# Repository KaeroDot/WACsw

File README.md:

# WACsw - software for Wideband AC quantum tracebility

Software and documentation for measurement method using Programmable Josephson Voltage Standard to calibrate AC voltage up to 100 kHz.
Developed in the scope of EPM project *23RPT01 WAC - Wideband AC quantum traceability*

[https://www.cem.es/es/WAC](https://www.cem.es/es/WAC)

## Links

[QWTB](https://qwtb.github.io/qwtb/)

[TWM](https://github.com/smaslan/TWM)

[TWM builds](https://github.com/smaslan/TWM-builds)

## Parts

### Filter function meter

*FFmeter* measures transfer function of a digitizer using AC-AC transfer method.

[Builds are here](https://github.com/KaeroDot/WACsw/tree/master/control_software/Filter%20function%20meter%20builds)

[How to install and run](https://github.com/KaeroDot/WACsw/blob/master/control_software/Filter%20function%20meter%20builds/How%20to%20install%20and%20run%20FFmeter.md)

### Data processing scheme

Scheme is in a [separate document](https://github.com/KaeroDot/WACsw/blob/master/doc/WACsw_requirements.md)

## Status of the project

Yet to do:

Type | Task | status
-----|------|--------
WACsw | basic structure | ✔
WACsw | schematics, templates | ✔
WACsw | measurement tests | ✔
WACsw | documentation | ½ (tooltips ok, how to ok, video missing)
WACsw | add calibrator Fluke 5720A | ✔
WACsw | add calibrator Fluke 5730A | ✔
WACsw | add source AFG3110C | ½ (not yet tested)
WACsw | add AC/DC standard corrections | ½ (works in script, missing in template)
WACsw | start result calculation from GUI (using script) | ✔
WACsw | finalize fitting of frequency response - find out best method | ✔ - splines
WACsw | ❗suggestion - alternate sampling and dc measurement instead of simultaneous | must be thought out
WACsw | ❗suggestion - measurement of sensitivity at the start | must be thought out
WACsw | ❗suggestion - implement K2182A nanovoltmeter | needed for PMJTC
WACsw | FR testing | ✔
WACsw | FR validation | ongoing
WACsw | CE testing | ✔
WACsw | CE validation | ongoing
WACsw | SS testing | ❌ - missing PJVS
WACsw | SS validation | ❌ - missing PJVS
processing FR | simulator | ✔
processing FR | simulator documentation | ❌
processing FR | processing | ✔
processing FR | processing documentation | ❌
processing FR | test | ✔
processing FR | test documentation | ❌
processing CE | simulator | ✔
processing CE | simulator documentation | ❌
processing CE | processing | ✔
processing CE | processing documentation | ❌
processing CE | test | ✔
processing CE | test documentation | ❌
processing SS | simulator | ✔
processing SS | simulator documentation  | ❌
processing SS | processing | ✔
processing SS | processing documentation  | ❌
processing SS | test | ✔
processing SS | test documentation  | ❌

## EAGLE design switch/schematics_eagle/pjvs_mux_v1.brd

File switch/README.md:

# Simple switch "PJVS Short MUX"

Two BNC inputs switch between BNC outputs:

```ascii
     ──●                             ──●            
Input1   ╲                      Input1              
     ──●  ╲                          ──●            
         ╲  ●──                             ●──     
          ╲   Output                      ╱   Output
            ●──                          ╱  ●──     
     ──●                             ──●  ╱         
Input2                          Input2   ╱          
     ──●                             ──●            
```

Actual required connection for sub-sampling with Device Under Test (DUT, i.e. AC source), Programmable Josephson Voltage Standard (PJVS) and digitizer:

To keep the short as short as possible, one input is shorted directly on the PCB.

This simple switch realize both "Switch" and "Box" in the PTB setup, as presented in paper [R. Behr and L. Palafox, ‘An AC quantum voltmeter for frequencies up to 100 kHz using sub-sampling’, Metrologia, vol. 58, no. 2, p. 025010, Mar. 2021, doi: 10.1088/1681-7575/abe453.](https://iopscience.iop.org/article/10.1088/1681-7575/abe453):

## Properties

- Controlled by:
  - DC signal >= 2.5 V
  - AC signal > 3 V peak-to-peak, frequency bandwidth larger than 10 MHz.
  - Manual control
- Can be controlled directly by National Instruments 5922 digitizer when using
10 MHz external clock. The clock is driven to PFI output on the digitizer and
used as AC signal to switch the relay.
- Input control signal is decoupled from rest of the circuit by an
opto-coupler.
- Powered by lithium 9 V battery that should last 17 years in idle mode.
- Bistable switching relay is double-pole, so the resistance should be very low.
- Two pieces of the switching relays can be mounted, however the
break-before-make will not be guaranteed and two relays are not suitable for
PJVS operation!
- Shielded part with AC control input to prevent interference with the rest of PCB.

The AC or DC control works only if the manual control switch is opened.

Print handle on 3D printer using [STL file](handle/handle.stl) and put it on
the BNC connectors on the side of digitizer for easier connecting to the
digitizer.

## Bill of materials

link | count    | note
---|---|---
[BAT-6F22-LT/GP](https://www.tme.eu/en/details/bat-6f22-lt_gp/batteries/gp/crv9-gp-b1/)    | 1  | any 9V battery, preferably lithium
[BS-ICCOMF-6F22](https://www.tme.com/in/en/details/bs-ic/batteries-containers-and-holders/comf/)    | 1  | 9 V battery connector
[EEUFC1C121](https://www.tme.com/in/en/details/eeufc1c121/tht-electrolytic-capacitors/panasonic/)        | 10 | C electrolyte 120u/16V d6.3mm
[EEUFR1E221](https://www.tme.com/in/en/details/eeufr1e221/tht-electrolytic-capacitors/panasonic/)        | 10 | C electrolyte 220u/25V d8mm low ESR
[G6KU-2F-Y-5DC](https://www.tme.com/in/en/details/g6ku-2f-y-5dc/miniature-electromagnetic-relays/omron-electronic-components/g6ku-2f-y-5vdc/)     | 1  | relay bistable 5V
[HM-1590B3](https://www.tme.com/in/en/details/hm-1590b3/multipurpose-enclosures/hammond/1590b3/)         | 1  | metal box
[7401SYZQE](https://www.tme.eu/en/details/7401syzqe/toggle-switches/c-k/)         | 1  | manual switch 4PDT
[PK10ASW](https://www.tme.com/in/en/katalog/?queryPhrase=PK10ASW)           | 1  | post 4mm earth
[031-10-RFXG1](https://www.tme.com/in/en/details/031-10-rfxg1/bnc-connectors/amphenol-rf/)      | 4  | BNC female isolated, panel mount
.                   | 2  | BNC male, panel mount
OK1 FOD817E         | 1  | opto-coupler PC817
Q1 BCV65            | 1  | general-purpose transistor BCV62
C 100p              | 1  | C EU025-024X044
C 1n                | 2  | C EUC0805K
C 100n              | 2  | C EUC0805K
D1 BAS40-04         | 1  | BAS40-04
D2 BAS32            | 1  | BAS32
IC1 40106D          | 1  | 40106D
R 4M7               | 1  | R EU_0207
R 1k                | 1  | R EU_R0805
R 51                | 2  | R EU_R0805
R 100               | 1  | R EU_R0805
R 2k2               | 2  | R EU_R0805
R 10k               | 1  | R EU_R0805

## Photos

### Soldered PCB

### HF shield

### Switch in the case

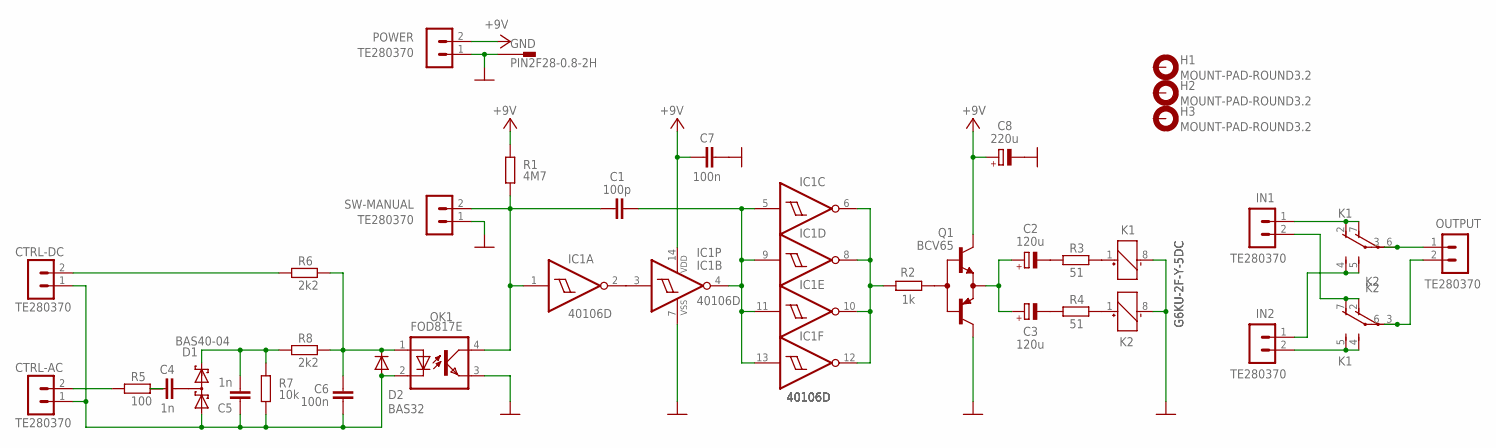
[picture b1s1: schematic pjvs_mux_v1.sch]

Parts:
C1: 100p; C025-024X044
C2, C3: 120u; E2,5-7
C4, C5: 1n; C0805K
C6, C7: 100n; C0805K
C8: 220u; E3,5-8
CTRL-AC: TE280370
CTRL-DC: TE280370
D1: BAS40-04; SOT23
D2: BAS32; SOD80C
GND: PIN2F28-0.8-2H; F28-0.8-2H
H1, H2, H3: MOUNT-PAD-ROUND3.2; 3,2-PAD
IC1: 40106D; SO14
IN1, IN2: TE280370
K1, K2: G6KU-2F-Y-5DC; G6KU-2F-Y
OK1: FOD817E; DIL04
OUTPUT: TE280370
POWER: TE280370
Q1: BCV65; SOT143
R1: 4M7; 0207/2V
R2: 1k; R0805
R3, R4: 51; R0805
R5: 100; R0805
R6, R8: 2k2; R0805
R7: 10k; R0805
SW-MANUAL: TE280370

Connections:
+9V: C7.1, C8.+, IC1.14 (VDD), POWER.2, Q1.1 (C1), R1.2
GND: C7.2, C8.-, GND.P$1, GND.P$2, IC1.7 (VSS), K1.8 (-), K2.8 (-), OK1.3 (EMIT), POWER.1, Q1.3 (C2), SW-MANUAL.1
unnamed: IC1.2 (O), IC1.3 (I)
unnamed: C1.2, IC1.4 (O), IC1.5 (I), IC1.9 (I), IC1.11 (I), IC1.13 (I)
unnamed: C1.1, IC1.1 (I), OK1.4 (COL), R1.1, SW-MANUAL.2
unnamed: IC1.6 (O), IC1.8 (O), IC1.10 (O), IC1.12 (O), R2.2
unnamed: Q1.2 (B), R2.1
unnamed: IN2.1, K1.4 (S), K2.5 (S)
unnamed: C2.-, R3.1
unnamed: K1.1 (+), R3.2
unnamed: C2.+, C3.+, Q1.4 (E)
unnamed: C3.-, R4.1
unnamed: K2.1 (+), R4.2
unnamed: IN1.1, K1.2 (O), K2.7 (O)
unnamed: K1.3, K2.6, OUTPUT.1
unnamed: IN2.2, K1.5 (S), K2.4 (S)
unnamed: IN1.2, K1.7 (O), K2.2 (O)
unnamed: K1.6, K2.3, OUTPUT.2
unnamed: C4.1, R5.2
unnamed: CTRL-AC.2, R5.1
unnamed: C4.2, D1.3 (C1A2)
unnamed: C5.1, C6.1, CTRL-AC.1, CTRL-DC.1, D1.1 (A1), D2.A, OK1.2 (C), R7.1
unnamed: C5.2, D1.2 (C2), R7.2, R8.1
unnamed: C6.2, D2.C, OK1.1 (A), R6.2, R8.2
unnamed: CTRL-DC.2, R6.1

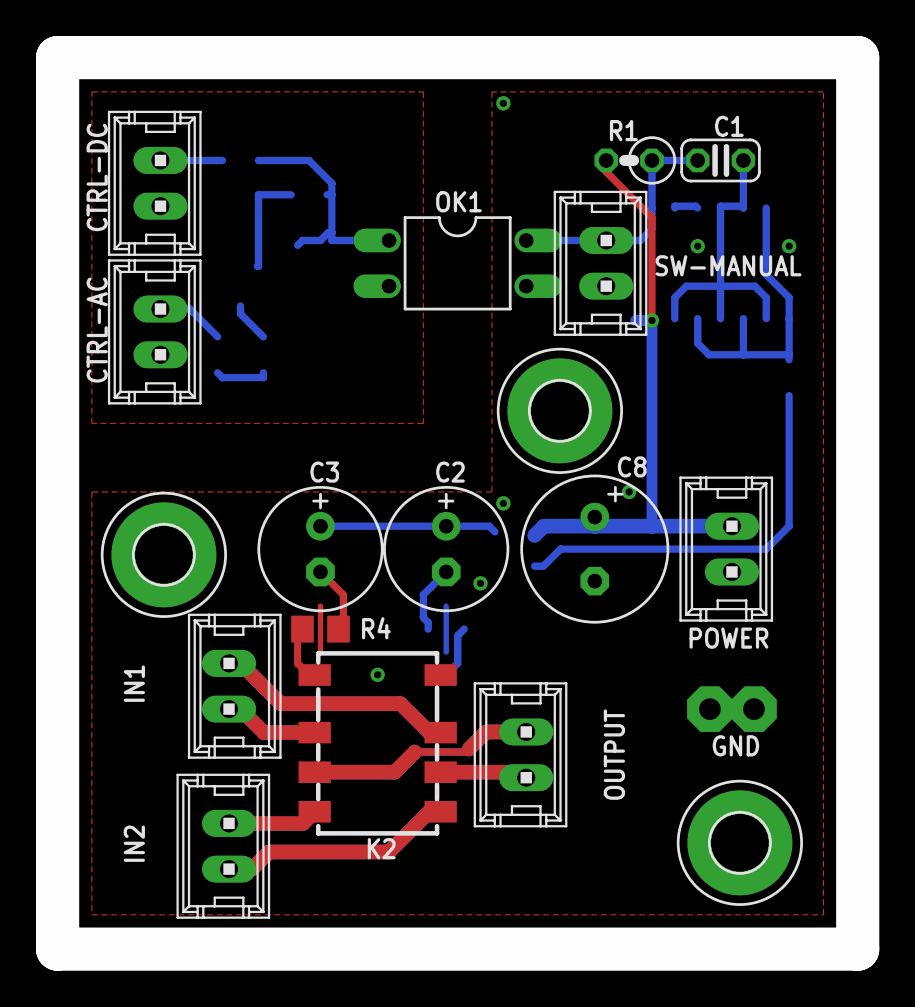
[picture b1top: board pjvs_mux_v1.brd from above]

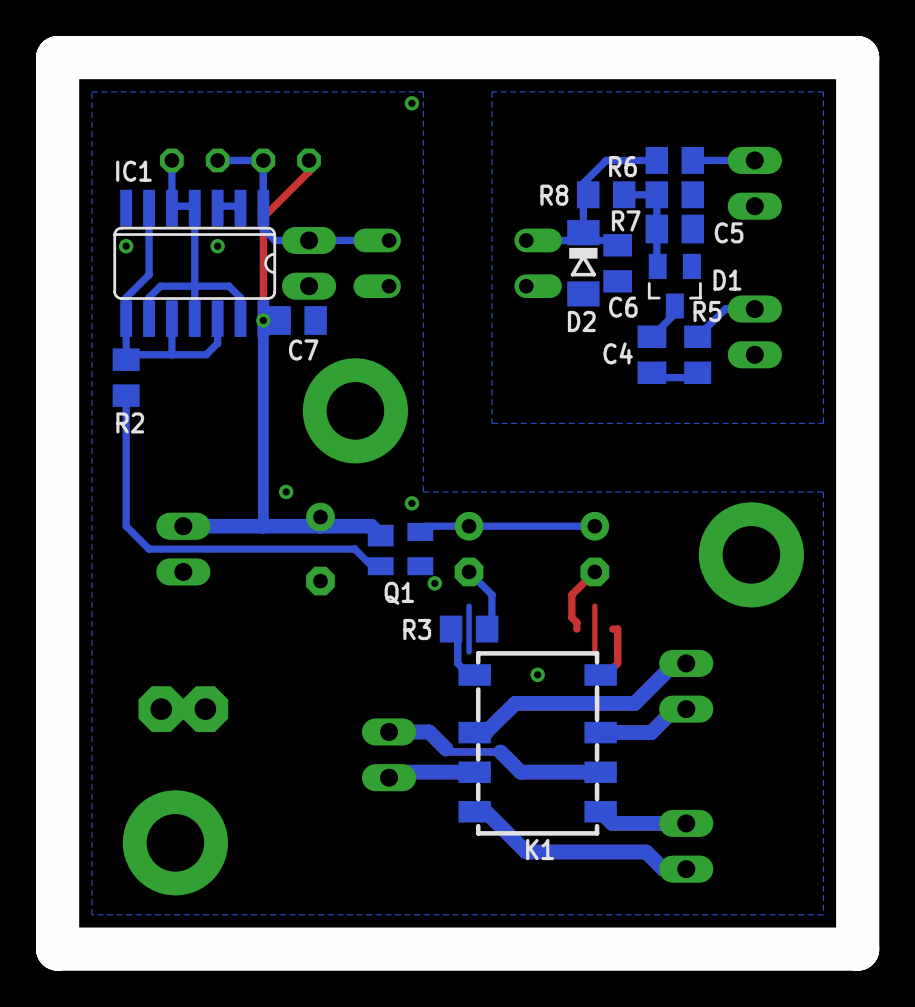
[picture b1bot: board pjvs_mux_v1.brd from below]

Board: 2 copper layers, 44.5 x 49.5 mm, 34 parts (15 on the bottom side), 25 nets.

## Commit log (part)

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2024-09-18 add: first version of software requirements and documentation
2024-09-18 add: figures into sw requirements
2024-10-14 add: alpha version of filter function meter
2024-10-16 add: continuous work
2024-10-18 add: FFmeter improved, almost finished
2024-10-18 add: FFmeter: logo as resource
2024-10-19 add: first script
2024-10-19 chng: update README
2024-11-13 FF meter: better XCL and GUI
2024-11-13 FFmeter: add measurement time estimate
2024-11-14 FFmeter: writes TWM results (if calculation set)
2024-11-14 FFmeter: ignore calculation errors and continue with measurement
2024-11-14 FFmeter: fix: proper amplitude for tektronix source
2024-11-17 add: FFmeter: script to calculate coherent frequencies
2024-11-17 FF processing: first scripts
2024-11-17 FFmeter: fix measurement time estimate
2024-11-17 FFmeter: build: v. 0.1.0.0
2024-11-22 FFmeter: fix: longer time outs for calculation
2024-11-22 FFmeter: add: warmup time
2024-12-02 FFmeter: add: skip waiting button
2024-12-02 FFmeter: add: connection diagram
2024-12-03 fix: FFmeter: better schematic diagram
2024-12-03 add: FFmeter: connections showin in GUI
2024-12-03 fix: FFmeter: dummy devices properly returns IDN
2024-12-03 add: FFmeter: measured data saved into folder with template
2024-12-10 add: FFmeter: recalculation of results, not yet working
2024-12-10 fix: FFmeter: HP3458 considered as tested
2024-12-10 fix: FFmeter: shows excel with template even if not started yet
2024-12-10 add: FFmeter: GOLPI library
2024-12-10 add: FFmeter: LVprocess library
2024-12-10 build: FFmeter: ver. 0.2
2024-12-12 fix: FFmeter: button colors on hover
2024-12-13 chng: FFmeter: DC meater readings parameter now in XCL template
2024-12-14 add: FFmeter: excel template properties as type definition
2024-12-15 add: FFmeter: algorithm settings in the template.
2024-12-17 fix: FFmeter: properly handle and skip TWM errors
2024-12-17 add: FFmeter: proper help in TWM setup
2024-12-18 fix: FFmeter: connection schematic
2024-12-18 fix: FFmeter: new connection schematic in the GUI
2024-12-22 fix: FFMeter: tooltips and details in template
2024-12-22 fix: FFmeter: again resetting TWM in case of error.
2024-12-22 fix: FFmeter: timeouts for calculation
2024-12-22 add: FFmeter: icon and window positions
2024-12-22 fix: FFmeter: details in template
2024-12-22 build: FFmeter: v.0.3.0.0
2024-12-23 add: FFmeter: how to install and setup
2025-01-23 add: working simulators of AC/DC standard and NI5922
2025-01-24 fix: FFmeter: setting AC source calibrator - proper frequency, no query check
2025-01-28 fully reworked and mostly working FR: frequency response
2025-01-28 add: pjvs_waveform_generator2.m
2025-01-31 add: new status of FF meter
2025-02-08 add: subsampling processing now working for proper sampling parameters
2025-02-11 add: continuation in not working SS
2025-02-11 fix: SS: limit of sampled values in processing
2025-02-12 add: working P_SS
2025-02-13 fix: working test example data
2025-02-13 fix: ensure nan package loaded in P_SS
2025-02-13 add: full example data, minimized to fit github
2025-02-13 fix: proper loading of SS example data
2025-02-13 fix: FR selftest
2025-02-14 add: FR processing: piecewise fitting (polynomial and spline)
2025-02-14 Create conditions_M_SS.m
    A short script to set sampling conditions and checking if they are acceptable.
2025-02-14 details in FR selftest
2025-02-17 fix: G_SS now takes input M_SS
2025-02-17 fix: piecewise fitting in test of example data
2025-02-17 add: fft filter in P_SS
2025-02-17 fix: G_SS bad structures
2025-02-17 add: SS selftest with fitler response
2025-02-17 chng README.md: current status update
2025-02-17 add: test_example_data description of final result
2025-02-20 fix: various small issues in reporting and plotting of P_SS
2025-03-11 add: frequency response documentation start
2025-03-11 P_SS: small fixes
2025-03-12 update status in README
2025-03-18 fix: GUI: proper name of Fluke57xx calibrators in type definition
2025-03-18 buid: FFmeter version 0.4.0.0
2025-03-18 chng: GUI: separation of TWM control into general VIs
2025-04-23 fix: proper reading from spreadsheet in FR, validation of data
2025-04-23 add: read FR from spreadsheet: swap rows in case someone measure first base than higher frequency
2025-04-23 add: README new goal
2025-04-26 FR: proper fitting only in the scope of measured data, better plotting
2025-04-28 FR: improved excell template with correct FR calculation (however no acdc corrections)
2025-04-30 FR GUI: added Keithley 2182
2025-04-30 FR GUI: possibility to measure simultaneously or sequentially
2025-05-02 FR GUI: added INRIM setup schematics
2025-05-02 build: FR GUI ver. 0.5.0.0
2025-05-23 forgotten change. Thank you NI for easy diff!
2025-06-27 gui: add: recalculation of FR template files
2025-06-27 doc: update for FR
2025-06-27 build: FR: ver.0.6.0.0
2025-06-28 chng: cleaner equation entry (no equation change) and better description
2025-06-30 fix: data processing takes new FR template
2025-07-07 GUI FR: fix default value transfer
2025-07-07 GUI FR: fix keep qwtb & octave paths
2025-07-08 FR GUI: all settings saved in Recalculate
    only changed type definition FFmeter settings and FR GUI Recalculate. All other are because of changed type definitions. Shame on LabView.
2025-07-08 CE GUI first version
2025-07-08 gitignore add excell temporary files
2025-07-08 AFG test
    vi for testing INRIM's AFG ac source and to find out communication issues. Stalled - wainting for INRIM response
2025-07-08 GUI: labview in proper path, FR builds also
2025-07-08 LV: renamed several files (no code change)
2025-07-08 FR GUI: icon fixes, build v.0.7.0.0
2025-07-08 LV: proper name of the project
2025-07-10 CE GUI: working CE measurement with temporary GUI, some TD changes
2025-07-11 GUI: add: super figure
2025-07-16 GUI: transition from FRmeter to general WACsw
2025-07-16 GUI: add: PJVS libraries and setup
2025-07-17 GUI: add SS setup
2025-07-17 GUI: fix in CE measurement
2025-07-18 GUI: SS now can measure CE before and after. Fixes in figure window
2025-07-18 GUI: add: manual controll of DCV, AC source and PJVS
2025-08-03 Fixed and finished manual vi showing, Agilent 33xx ac sources.
2025-08-03 build: first version of WACsw
2025-08-04 GUIL Proper names of windows, better look of PJVS setup
2025-08-06 proc: proper names for selftests
2025-08-06 proc: fix paths for ACDC corrections, help in G_SS
2025-08-06 doc: proper page size
2025-08-06 proc: clean up of PJVS generators
2025-09-24 add: processing: CE, in development
2025-10-22 add: files for PJVS simple mux
2025-10-23 improved help in selftest
2025-10-24 better cable error simulation script
2025-10-26 add: working cable error generator
2025-11-03 add: data_processing: SS_selftest with CE_fit
2025-11-03 chng: data processing: better naming of CE_fit functions
2025-11-04 proper naming in CE functions, CE returns voltage ratio instead of error
2025-11-04 data processing: CE takes FR_fit as part of structure
2025-11-05 lvprog: added utility files for transition to CE excell template
2025-11-06 lvsource: CE GUI changed to template
2025-11-08 add: CE template added missing cable lenghts and FR fit path
2025-11-09 add: final version of the CE example sheet with cable lengths and comments
2025-11-09 fix: data processing reads new CE template. model function converted to string. CE and FR exports to mat.
2025-11-12 add: lv: writing and recalculating CE spreadsheet
2025-11-12 data processing: script to seach coherent freqs
2025-11-14 add: lvsource: control now correctly calculates FR, CE fits from spreadsheet
2025-11-14 opravene programy
    opravil som piecewise fr fit a variate fr regions ale vyhadzuje mi to nejaky zvlastny graf aj ked funkcia by mala byt identicka.
2025-11-17 lv: fix: working repeated octave calculations in FR and CE
2025-11-17 data: add example FR and CE
2025-11-18 opravene programy piecewise_FR_fit a regions
2025-11-18 lv: fix: proper paths in octave for data processing vs TWM
2025-11-18 lv: working CE measurements for SS measurement
2025-11-18 data processing: various notes and little details
2025-11-18 data_processing: fix: M_FR label
2025-11-19 lv: add: ac source fluke wideband output
2025-11-19 lv: add: synchronisation for ac source
2025-11-19 lv: fix ac sync source, working and tested for Fluke 5720
2025-11-19 lv: fix: paths to templates, scripts, lvproc.dll
2025-11-20 add: script to generate table for CE measurements
2025-11-21 lv: add: saving SS data, not yet ready
2025-11-21 lv: build: ver 0.2.0.0
2025-11-23 lv: add: working saving of SS data
2025-11-23 add: proc: reading of sampled data
2025-11-25 lv: add: working calculation of SS
2025-11-28 lv: various fixes
2025-11-28 lv: sampling triggered by level dc 0 V
2025-11-28 lv: build: ver. 0.2.1.0
2025-12-31 fix: proper order of input variables in piecewise_FR_fit
2025-12-31 improved variate_FR_regions.m
2025-12-31 chng: proper name and simplification of variate_FR_measurement_points
2026-01-01 refactor G_FR to take input with simulation parameters and errors
2026-01-21 fix-add: controlling broken F5XXX - possibility to ignore error, properly check set values of AC source
2026-01-28 fix: no errors for Fluke5730 and notes about wideband&phaselock incompatibility
2026-01-28 fix: FR templates improved plotting in xls
2026-01-28 build: ver. 0.2.2.0
2026-02-02 add github copilot instructions
2026-02-12 add: dataproc: FR: regions part of M_SS
2026-02-12 improved copilot instructions
2026-02-12 data_proc: proper check set environment, utilities moved to utils directory
2026-02-15 proper variate scripts
2026-02-20 fix: small changes in FR excell templates (figure data span, cosmetics)
2026-02-20 add: variate_FR_error export to csv
2026-02-23 FR xls templates with reference data
2026-05-11 note to G_FR
2026-05-21 update info on switch, pictures, details
2026-05-21 Create Example of CE meter template 4 MHz fast.xlsx
    add: fast version of CE meter template
2026-05-21 add: note in GUI FIXME
2026-05-21 fix: GUI: correct amplitude for A33120 series
2026-05-27 fix: proper path to FR fit files in CE template
2026-05-28 gui: reworked CE template handling for SS measurement
2026-05-28 GUI: SS calculation moved after all CE measurments
2026-05-29 add: improved switch handle, new photos
2026-05-29 fix: proper 3D file of switch handle
2026-05-29 add: CE fit can handle also single point CE measurement. added demo and tests
2026-06-01 fix: CE fit single point meas. without adding zero f meas.
2026-06-02 fix: read SS data with relative paths
2026-06-04 GUI: correctly calling SS calculation, displaying Arms result.
2026-06-04 build: GUI ver. 0.3.0.0
2026-06-04 add: GUI: JV PJVS settings default values
2026-06-04 fix: GUI: PJVS manual control also for NPL Bias source
2026-06-07 add: script to calculate gain of digitizer
2026-06-08 fix: GUI: NPL PJVS settings writable
2026-06-08 build: GUI v.0.3.1.0
2026-06-09 fix: GUI: PJVS test shows error if happens
2026-06-09 build: GUI: 0.3.2
2026-06-11 note in P_CE
2026-06-11 add: FR: recalculate FR measurements
2026-06-11 add: evaluation scripts
2026-06-11 add: G_CE takes input S_CE for simulation parameters
2026-06-12 GUI: adding help to VIs, removed old VIs.
2026-06-18 add: first scripts for digitizer calibration (DC)
2026-06-19 add: finished G_DC.m
2026-06-19 fixes in DC scripts
2026-06-19 fix in triangle generator proper matrix generation
2026-06-19 better help in DC scripts, added DC into check_and_set_environment
2026-06-19 Update copilot-instructions.md for DC
2026-06-19 preparation of selftest_SS for DC
2026-06-20 change DC (digitizer calibration) to DG (digitizer gain) to prevent mixup with DC as direct current
2026-06-23 GUI: first version with digitizer gain measurement
2026-06-24 add: reading DG measured data
2026-06-25 GUI: working, tested DG
2026-06-25 P_DG better verbose output
2026-06-25 GUI: DG measurement reports result
2026-06-26 fix: GUI: saving SS info
2026-06-26 fix: proper scaling of TWM data, correct repmat, Upjvs vs Upjvs1period
2026-06-30 GUI: build: ver. 3.3.0
2026-06-30 build: missing lib and data_processing in last build
